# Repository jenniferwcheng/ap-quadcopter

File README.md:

# IEEE@UCLA Advanced 2017-2018
Quadcopter

## Process:
* Select Pro Mini in Aruduino IDE
* Compile + Upload
* If it doesn't work, try pressing/holding the reset button on the board between compile and upload

## Layout of Motors:
```
RB = Red/Blue
BW = Black/White
RB BW
BW RB
```

## TO-DO:
* Figure out ports and #define them all
* Crimp motor wires and attach them via female JST to board
* Get battery and test individual motor (analogWrite to control speed)
* Attach all motors to plastic body
* Try flying while held down with all 4 motors and rotors
* Attach gyroscope/accelerometer
* Do actual error correction + control using sensors
* Attach radio
* Implement radio control

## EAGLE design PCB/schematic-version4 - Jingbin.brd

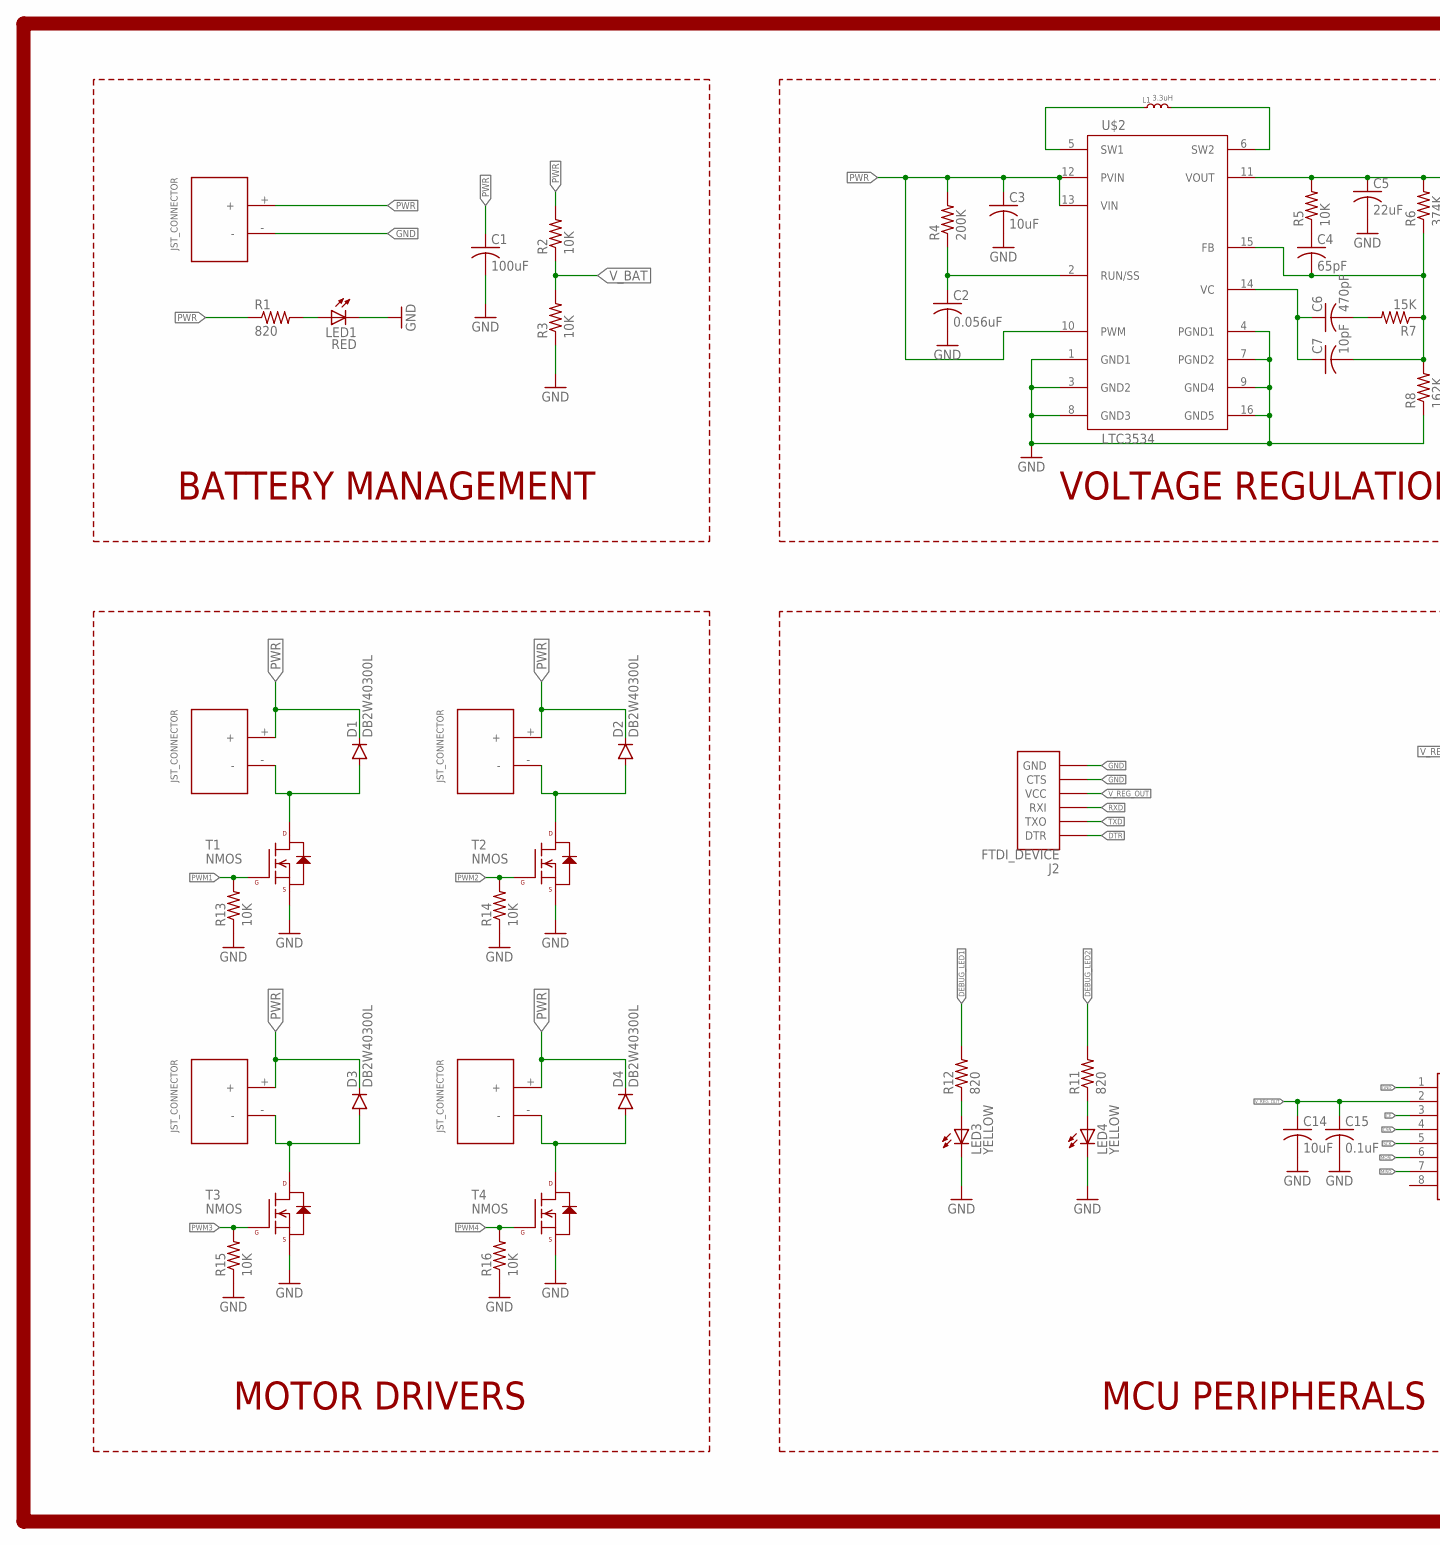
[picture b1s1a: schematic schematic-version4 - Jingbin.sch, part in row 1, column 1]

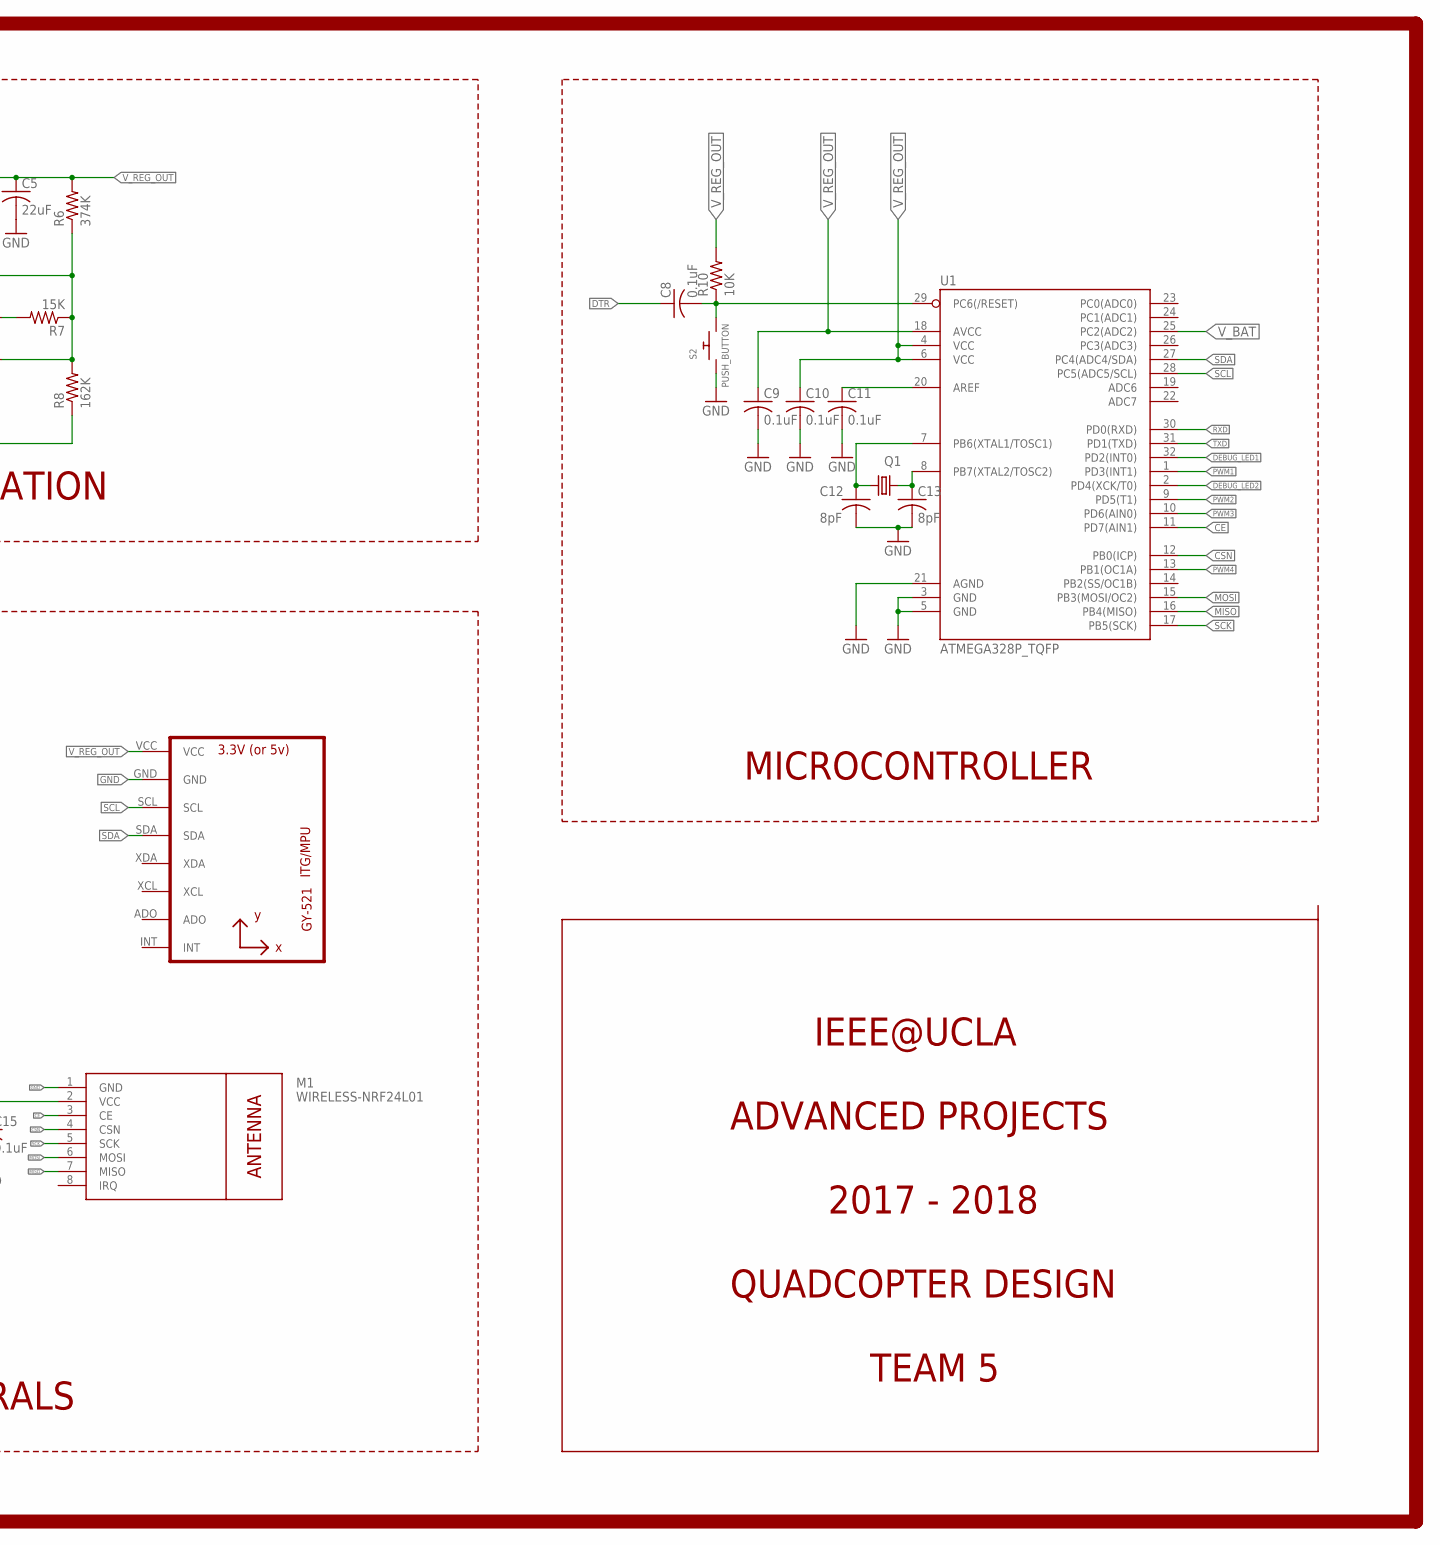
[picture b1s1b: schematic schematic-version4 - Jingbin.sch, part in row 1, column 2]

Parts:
C1: 100uF; C1206
C2: 0.056uF; C0603
C3, C14: 10uF; C0603
C4: 65pF; C1206
C5: 22uF; C0603
C6: 470pF; C0603
C7: 10pF; C0603
C8, C9, C10, C11, C15: 0.1uF; C0603
C12, C13: 8pF; C0603
D1, D2, D3, D4: DB2W40300L; MINI2-F3-B
J2: FTDI_DEVICE; FTDI_DEVICE_SIDE
L1: 3.3uH; XAL4020
LED1: RED; SML0603
LED3, LED4: YELLOW; SML0603
M1: WIRELESS-NRF24L01
Q1: NX3225GD; NX3225GD-CRA-3
R1, R11, R12: 820; R0603
R2, R3, R5, R10, R13, R14, R15, R16: 10K; R0603
R4: 200K; R0603
R6: 374K; R0603
R7: 15K; R0603
R8: 162K; R0603
S2: PUSH_BUTTON; PUSHBUTTON_SMD_SJ
T1, T2, T3, T4: NMOS; SOT23-3
U1: ATMEGA328P_TQFP; TQFP32-08
U2: GY-521MPU6050; GY-521
U$1, U$4, U$7, U$10, U$13: JST_CONNECTOR_FEMALE
U$2: LTC3534; SSOP-16GN

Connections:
CE: M1.3 (CE), U1.11 (PD7(AIN1))
CSN: M1.4 (CSN), U1.12 (PB0(ICP))
DEBUG_LED1: R12.2, U1.32 (PD2(INT0))
DEBUG_LED2: R11.2, U1.2 (PD4(XCK/T0))
DTR: C8.1, J2.P$1 (DTR)
GND: C1.2, C2.2, C3.2, C5.2, C9.2, C10.2, C11.2, C12.2, C13.2, C14.2, C15.2, J2.P$5 (CTS), J2.P$6 (GND), LED1.C, LED3.C, LED4.C, M1.1 (GND), R3.1, R8.1, R13.1, R14.1, R15.1, R16.1, S2.P$1, T1.2 (S), T2.2 (S), T3.2 (S), T4.2 (S), U1.3 (GND), U1.5 (GND), U1.21 (AGND), U2.GND, U$1.-, U$2.1 (GND1), U$2.3 (GND2), U$2.4 (PGND1), U$2.7 (PGND2), U$2.8 (GND3), U$2.9 (GND4), U$2.16 (GND5)
MISO: M1.7 (MISO), U1.16 (PB4(MISO))
MOSI: M1.6 (MOSI), U1.15 (PB3(MOSI/OC2))
unnamed: C12.1, Q1.P$1 (1), U1.7 (PB6(XTAL1/TOSC1))
unnamed: C8.2, R10.1, S2.P$2, U1.29 (PC6(/RESET))
unnamed: D1.POS (PPIN), T1.3 (D), U$4.-
unnamed: C13.1, Q1.P$2 (2), U1.8 (PB7(XTAL2/TOSC2))
unnamed: D2.POS (PPIN), T2.3 (D), U$7.-
unnamed: D3.POS (PPIN), T3.3 (D), U$10.-
unnamed: D4.POS (PPIN), T4.3 (D), U$13.-
unnamed: L1.1, U$2.5 (SW1)
unnamed: L1.2, U$2.6 (SW2)
unnamed: LED1.A, R1.2
unnamed: LED3.A, R12.1
unnamed: LED4.A, R11.1
unnamed: C4.1, R5.1
unnamed: C2.1, R4.1, U$2.2 (RUN/SS)
unnamed: C4.2, C7.2, R6.1, R7.1, R8.2, U$2.15 (FB)
unnamed: C6.1, C7.1, U$2.14 (VC)
unnamed: C6.2, R7.2
unnamed: C11.1, U1.20 (AREF)
PWM1: R13.2, T1.1 (G), U1.1 (PD3(INT1))
PWM2: R14.2, T2.1 (G), U1.9 (PD5(T1))
PWM3: R15.2, T3.1 (G), U1.10 (PD6(AIN0))
PWM4: R16.2, T4.1 (G), U1.13 (PB1(OC1A))
PWR: C1.1, C3.1, D1.NEG (GPIN), D2.NEG (GPIN), D3.NEG (GPIN), D4.NEG (GPIN), R1.1, R2.2, R4.2, U$1.+, U$2.10 (PWM), U$2.12 (PVIN), U$2.13 (VIN), U$4.+, U$7.+, U$10.+, U$13.+
RXD: J2.P$3 (RXI), U1.30 (PD0(RXD))
SCK: M1.5 (SCK), U1.17 (PB5(SCK))
SCL: U1.28 (PC5(ADC5/SCL)), U2.SCL
SDA: U1.27 (PC4(ADC4/SDA)), U2.SDA
TXD: J2.P$2 (TXO), U1.31 (PD1(TXD))
V_BAT: R2.1, R3.2, U1.25 (PC2(ADC2))
V_REG_OUT: C5.1, C9.1, C10.1, C14.1, C15.1, J2.P$4 (VCC), M1.2 (VCC), R5.2, R6.2, R10.2, U1.4 (VCC), U1.6 (VCC), U1.18 (AVCC), U2.VCC, U$2.11 (VOUT)

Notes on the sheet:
BATTERY MANAGEMENT
VOLTAGE REGULATION
MOTOR DRIVERS
MCU PERIPHERALS
MICROCONTROLLER
IEEE@UCLA
ADVANCED PROJECTS
2017 - 2018
QUADCOPTER DESIGN
TEAM 5

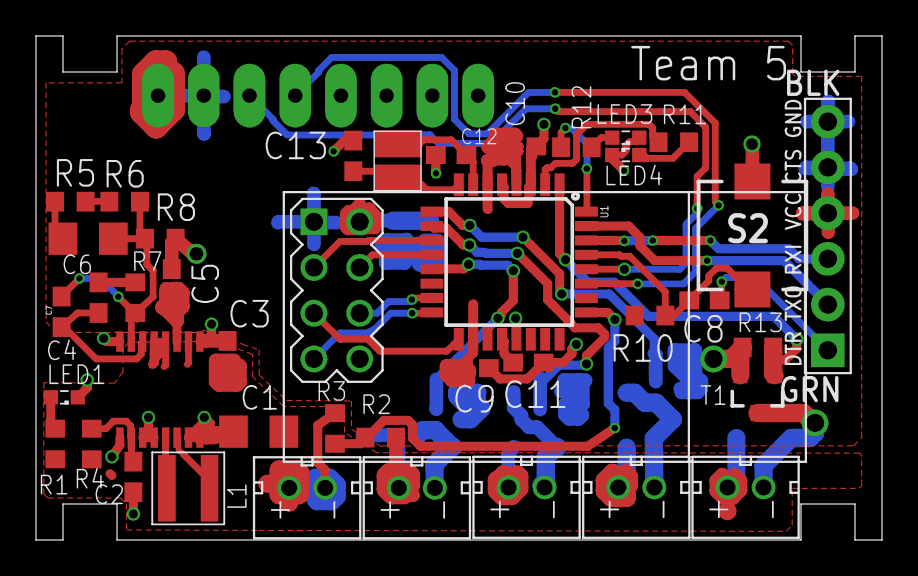
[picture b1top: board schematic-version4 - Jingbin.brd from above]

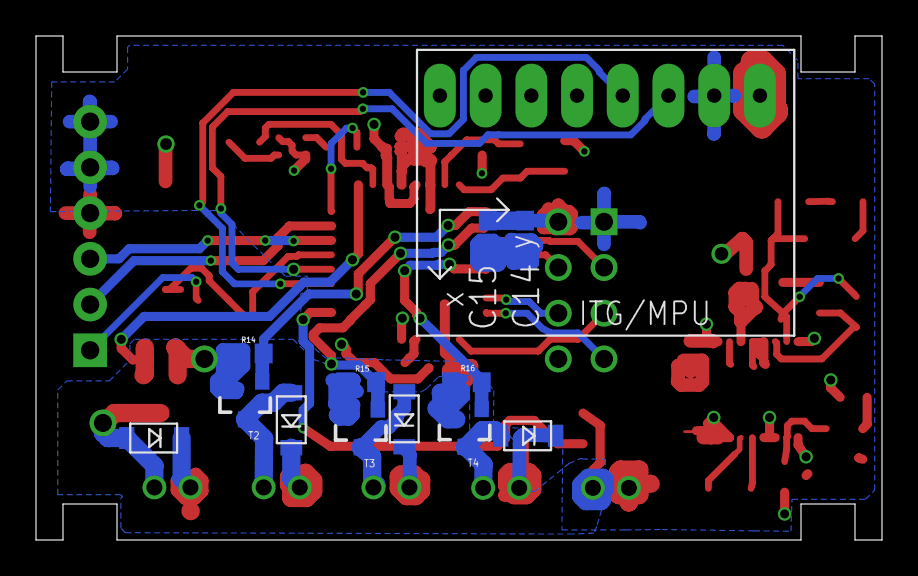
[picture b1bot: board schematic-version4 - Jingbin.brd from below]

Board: 2 copper layers, 47.0 x 28.0 mm, 54 parts (13 on the bottom side), 38 nets.

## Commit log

2018-01-24 added readme
2018-01-24 Added sensor, RF
    Need work on voltage regulator, header for FDTI, more decoupling,
2018-01-25 Added (mostly compelte) v-reg circuit
2018-01-25 completed v_reg external, decouplng, labels
    Need work on adding control switches, indicator LEDs. Need to find all correct parts and replace current placeholder symbols
2018-01-25 added ap libraries for easier access
2018-01-26 Added LEDs, switches, motor circuit, and made it look pretty
    Still need to get all the correct parts to replace place-holder
2018-01-26 added pull-down for motor
2018-01-26 Fixed all warnings, added more debug LEDs
2018-01-27 Added load capacitor for crystal
2018-01-27 SOmething
2018-01-28 Updated parts to reflect actual selection
2018-01-28 Changed voltage divider values
2018-01-28 added slide switch
2018-01-28 Included libraries for some parts
    Adafruit for push button.
    Coilcraft for inductor used in voltage regulator.
    Wurth for sliding switch
2018-01-28 Fixed spelling, standardized label sizing
2018-01-30 Removed switch, changed some names, removed an unnecessary capacitor
    Changed power from battery to PWR instead of VCC, to be exact
2018-01-31 Fixed issues mentioned in design review
    Changed voltage divider resistors to 10K.
    Got new voltage regulator, completely circuit and PCD footprint.
    Changed all component package to 0603.
2018-02-01 Fixed issues from schematic pre-check
    Changed package of R15,R16 to 0603.
    CHange 100pF capacitor to 68pF to be closer to recommended value.
2018-02-02 65pF capacitor 1206 package
2018-02-02 fixed programmer RX TX
2018-02-03 Fixed LED package
2018-02-07 started PCB design
2018-02-07 Started PCB design
    Current plan: motor driver on bottom, RF module on bottom, need to space out top to make room for reset push button and debug LED
2018-02-08 Restarting design
2018-02-08 PCB First Draft done
    No errors
2018-02-09 changed pwm routes to 20 width and fixed clearance
    should do polygons for gnd and power
2018-02-10 Made some changes according to review notes
    Fixed FTDI connector, added keepout outline to voltage regulator. Changes are reflected in version2 file. version2 board is empty for you routing pleasure.
2018-02-10 Oops
2018-02-12 Started a layout attempt
2018-02-13 Added anohter finished version
    Need to fix clearence issues
2018-02-13 Fixed problems in my version 2
2018-02-13 Changed V_BAT trace from thin to thic
2018-02-14 Another draft
    Radio on top, IMU on bottom. Ground plane on bottom. Left half of top plane is PWR, for motor needs. Right half of top plane is regulated output, for MCU, radio, and IMU needs.
2018-02-15 Yet another attempt
    Pretty much no bottleneck, but have components under IMU, need fix
2018-02-15 Version 4 complete
2018-02-15 More adjustments to widen some paths and ensure multiple connection
2018-02-15 added archive folder
2018-02-16 checked with osh park drc file
2018-02-16 Added new crystal
2018-02-16 More adjustments to version4, version5 is empty
2018-02-20 made more space for vregout
2018-02-20 More space for VREGOUT near voltage regulator
2018-02-20 Fixed DRC error in previous commit
2018-02-20 More paths, hopefully less bottleneck
2018-02-20 Slightly adjusted trace thickness
2018-02-20 Moved radio decoupling capacitor closer to radio power
2018-02-20 More finer adjustments
2018-02-20 I swear it's the last time
2018-02-20 More paths...
2018-02-21 More thicc paths
2018-02-21 Added silkscreen
2018-02-21 Removed thermal for motor 4
2018-02-25 Change 100uF capacitor size
2018-05-31 lit up LED3
2018-06-05 Basic documentation + todo
2018-06-05 formatting of readme
2018-06-05 Defined ports in INO file
2018-06-05 test motor
2018-06-05 added sensor fusion code
2018-06-06 commented out gryo code

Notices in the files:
parts and their libraries:
SparkFun: Licensing: CC v3.0 Share-Alike You are welcome to use this library for commercial purposes.
